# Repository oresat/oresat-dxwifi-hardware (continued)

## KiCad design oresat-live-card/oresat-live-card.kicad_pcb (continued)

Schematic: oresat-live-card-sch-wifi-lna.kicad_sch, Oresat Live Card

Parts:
C90, C91, C93: 15p; 0402-C-NOSILK; MPN GJM1555C1H150JB01D
C92: 1u; 0603-C-NOSILK; MPN GRT188R71E105KE13D
C106, C111: 0.1u; 0603-C-NOSILK; MPN C0603C104K5RACAUTO
C107, C114: 100p; 0402-C-NOSILK; MPN GCM1555C1H101GA16D
C108: 1n; 0402-C-NOSILK; MPN C0402C102J1GACTU
C109: 1n; 0402-C-NOSILK; MPN CGA2B2NP01H102J050BA
C110: 1p; 0402-C-NOSILK; MPN GCM1555C1H1R0CA16J
C112, C113: 100n; 0402-C-NOSILK; MPN CGA2B3X7R1E104K050BB
D15: GRN; LED-0603; MPN 150060GS75000
FL1, FL2: QPQ1907SR; MPN QPQ1907SR
L3: 18n; 0603-C-NOSILK; MPN 0603DC-18NXJRW
L4: 1.5n; 0402-C-NOSILK; MPN 0402HM-1N5EKTS
R85: 4.7k; 0603-C-NOSILK; MPN RMCF0603FT4K70
R88: 10k; 0603-C-NOSILK; MPN RMCF0603FT10K0
R105: 33k; 0603-C-NOSILK; MPN RMCF0603FT33K0
R106: 0; 0402-C-NOSILK; MPN RMCF0402ZT0R00
R109: 56; 0603-C-NOSILK; MPN ERJ-3EKF56R0V
R118, R119, R120: 4.99k; 0603-C-NOSILK; MPN RMCF0603FT4K99
R121: 100; 0603-C-NOSILK; MPN RMCF0603FT100R
TP26: TEST-POINT3X4; TestPoint-0.75mm-th
U18: TQP3M9037; DFN-8-1EP_2x2mm_P0.5mm_EP0.8x1.6mm; MPN TQP3M9037
U27: PAT1220-C-3DB; RF_Attenuator_Susumu_PAT1220; MPN PAT1220-C-3DB-T5
U28: PD2328J5050S2HF; MPN PD2328J5050S2HF
U29: LTC5538; DFN-8-1EP_3x3mm_P0.5mm_EP1.65x2.38mm; MPN LT5538IDD#TRPBF

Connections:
5VA: C106.2, C107.1, C112.2, C113.2, C114.1, R106.2, R118.1, U29.5 (VCC); also elsewhere on the board
/SIP B: ADC + Crystals/RF/RX_IN_DETECTED: C111.1, R119.2, R120.2, TP26.1 (1_1); also elsewhere on the board
/WiFi LNA/AR9271_RX: R121.1, U28.4 (OUTPUT1); also elsewhere on the board
/WiFi LNA/LNA_SHUTDOWN: R85.1, R105.1; also elsewhere on the board
/WiFi LNA/RX_FROM_SWITCH: FL1.1 (INPUT); also elsewhere on the board
GND: C91.2, C92.2, C106.1, C107.2, C108.2, C110.1, C111.2, C114.2, D15.1 (K), FL1.2 (GND), FL1.3 (GND), FL1.5 (GND), FL2.2 (GND), FL2.3 (GND), FL2.5 (GND), R88.2, R109.2, R120.1, U18.9 (GND), U27.3, U28.1 (GND), U28.3 (GND), U28.5 (GND), U29.4 (GND), U29.9 (GND); also elsewhere on the board
unnamed: C91.1, C92.1, L3.1, R106.1
unnamed: C93.2, U27.1
unnamed: C109.1, L4.2, R109.1
unnamed: D15.2 (A), R85.2
unnamed: C90.1, FL1.4 (OUTPUT)
unnamed: FL2.1 (INPUT), U27.2
unnamed: FL2.4 (OUTPUT), U28.2 (INPUT)
unnamed: C90.2, U18.2 (RF_IN)
unnamed: C93.1, L3.2, U18.7 (RF_OUT)
unnamed: R88.1, R105.2, U18.6 (SHUT_DOWN)
unnamed: C110.2, L4.1, R121.2, U28.6 (OUTPUT2)
unnamed: C113.1, U29.7 (CAP+)
unnamed: C112.1, U29.6 (CAP-)
unnamed: R118.2, U29.1 (EN)
unnamed: C109.2, U29.2 (IN+)
unnamed: C108.1, U29.3 (IN-)
unnamed: R119.1, U29.8 (OUT)

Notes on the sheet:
~ 1.65 V max which is < 1.8 V of Octavo ADC max
0402
Changed from 100 to 56
~ 3 V max
RF Detector, transforms RF detected into a DC sense line for Octavo to read
All resistors 0603 +/- 1% unless marked and AEQ certified unless otherwise marked. All caps are 0603 10% X5R or better and Vw >= 25 V and AEQ certified unless otherwise marked.
"LNA OFF"

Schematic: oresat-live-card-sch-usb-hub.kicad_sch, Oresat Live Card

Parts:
C1, C27, C28, C42, C54, C55, C56, C57, C58, C59, C60, C65, C66, C67, C68, C70, C71, C72: 0.1u; 0603-C-NOSILK; MPN C0603C104K5RACAUTO
C53, C69, C76, C96, C97: 10u; 0805-C-NOSILK; MPN GRT21BC71E106KE13K
C63, C64: 12p; 0603-C-NOSILK; MPN C0603C120J1GACTU
C73: 1u; 0603-C-NOSILK; MPN GRT188R71E105KE13D
D10: GRN; LED-0603; MPN 150060GS75000
FB1, FB3: BLM18KG300TH1D; 0603; MPN BLM18KG300JH1D
FB4, FB5: MMZ1608Y221BTD25; 0603; MPN MMZ1608Y221BTD25
R6, R7, R21, R76, R77, R79, R89, R90, R91: 10k; 0603-C-NOSILK; MPN RMCF0603FT10K0
R29: 4.7k; 0603-C-NOSILK; MPN RMCF0603FT4K70
R78: 9.53k; 0603-C-NOSILK; MPN RMCF0603FT9K53
R83: 90.9k; 0603-C-NOSILK; MPN RMCF0603FT90K9
R98, R99: 0; 0603-C-NOSILK; MPN RMCF0603ZT0R00
TP1, TP15: TEST-POINT; TestPoint_Pad_D1.0mm
TP13, TP16, TP17, TP18: TEST-POINT3X4; TestPoint_Pad_D1.0mm
U2: TUSB4020BI; TQFP-48-1EP_7x7mm_P0.5mm_EP5x5mm; MPN TUSB4020BIPHPRQ1
U9, U20: TPS2041BQDBVRQ1; DBV5; MPN TPS2041BQDBVRQ1
Y3: 24MHz; 5X3.2-4SMD; MPN ECS-240-12-30BQ-AEN-TR

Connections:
1.1V: FB4.2; also elsewhere on the board
+3.3V: FB5.2, R6.2, R7.2, R77.1, R79.2, R90.2, R91.2; also elsewhere on the board
+5V: R98.2, R99.2; also elsewhere on the board
/SIP B: ADC + Crystals/UP_N: U2.27 (USB_DM_UP); also elsewhere on the board
/SIP B: ADC + Crystals/UP_P: U2.26 (USB_DP_UP); also elsewhere on the board
/SIP B: ADC + Crystals/USB_VBUS: R83.1; also elsewhere on the board
/SIP C: SD + eMMC + CAN/GRSTz: R89.2, U2.11 (GRSTz); also elsewhere on the board
/USB HUB/CAMERA_USB_N: U2.42 (USB_DM_DN1); also elsewhere on the board
/USB HUB/CAMERA_USB_P: U2.41 (USB_DP_DN1); also elsewhere on the board
/USB HUB/CAMERA_VUSB: FB3.2, TP1.1 (1_1); also elsewhere on the board
/USB HUB/WIFI_ENABLE: R29.1; also elsewhere on the board
/USB HUB/WIFI_STATUS: D10.1 (K); also elsewhere on the board
/USB HUB/WIFI_USB_N: U2.15 (USB_DM_DN2); also elsewhere on the board
/USB HUB/WIFI_USB_P: U2.14 (USB_DP_DN2); also elsewhere on the board
/USB HUB/WIFI_VUSB: FB1.2, R21.1, R29.2, TP15.1 (1_1); also elsewhere on the board
GND: C1.2, C27.2, C28.2, C42.2, C53.2, C54.2, C55.2, C56.2, C57.2, C58.2, C59.2, C60.2, C63.2, C64.2, C65.2, C66.2, C67.2, C68.2, C69.2, C70.2, C71.2, C72.2, C73.2, C76.2, C96.2, C97.2, R76.1, R78.2, R89.1, U2.10 (TEST), U2.49 (GND), U9.2 (GND), U20.2 (GND), Y3.2 (G), Y3.4 (G); also elsewhere on the board
unnamed: C54.1, C55.1, C57.1, C59.1, C65.1, C67.1, C69.1, FB4.1, U2.1 (VDD), U2.12 (VDD), U2.18 (VDD), U2.30 (VDD), U2.34 (VDD), U2.45 (VDD)
unnamed: D10.2 (A), R21.2
unnamed: TP13.1 (1_1), U2.36 (FULLPWRMGMTz/SMBA1)
unnamed: R79.1, U2.35 (GANGED/SMBA2/HS_UP)
unnamed: R91.1, U2.5 (OVERCUR1z), U20.3 (~OC)
unnamed: R6.1, U2.8 (OVERCUR2z), U9.3 (~OC)
unnamed: R90.1, U2.4 (PWRCTL1/BATEN1), U20.4 (~EN)
unnamed: R7.1, U2.6 (PWRCTL2/BATEN2), U9.4 (~EN)
unnamed: R77.2, U2.21 (PWRCTL_POL)
unnamed: TP17.1 (1_1), U2.2 (SCL/SMBCLK)
unnamed: TP16.1 (1_1), U2.3 (SDA/SMBDAT)
unnamed: TP18.1 (1_1), U2.22 (SMBUSz)
unnamed: R78.1, U2.24 (USB_R1)
unnamed: R76.2, R83.2, U2.9 (USB_VBUS)
unnamed: C63.1, U2.38 (XI), Y3.1
unnamed: C64.1, U2.39 (XO), Y3.3
unnamed: C1.1, R98.1, U9.5 (IN)
unnamed: C27.1, C53.1, C96.1, FB3.1, U9.1 (OUT)
unnamed: C28.1, R99.1, U20.5 (IN)
unnamed: C42.1, C76.1, C97.1, FB1.1, U20.1 (OUT)
VDD33: C56.1, C58.1, C60.1, C66.1, C68.1, C70.1, C71.1, C72.1, C73.1, FB5.1, U2.7 (VDD33), U2.13 (VDD33), U2.23 (VDD33), U2.25 (VDD33), U2.33 (VDD33), U2.37 (VDD33), U2.40 (VDD33), U2.48 (VDD33)

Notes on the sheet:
Wifi USB
Ordering of ferrite bead and capacitor taken from TPS2041 datasheet (see figure 9-13)
Assert GRSTz via GPIO to deactivate USB hub and clear registers
Camera USB
"WIFI"
All resistors 0603 +/- 1% unless marked and AEQ certified unless otherwise marked. All caps are 0603 10% X5R or better and Vw >= 25 V and AEQ certified unless otherwise marked.

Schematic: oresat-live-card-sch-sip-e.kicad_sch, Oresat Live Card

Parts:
U7: OSD3358-512M-BSM; U-Octavo-OSD335X-BGA-256; MPN OSD3358-512M-BSM

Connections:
GND: U7.D8 (DGND@1), U7.D9 (DGND@2), U7.E5 (DGND@3), U7.E6 (DGND@4), U7.E7 (DGND@5), U7.E8 (DGND@6), U7.E9 (DGND@7), U7.E10 (DGND@8), U7.E11 (DGND@9), U7.E12 (DGND@10), U7.F5 (DGND@11), U7.F12 (DGND@12), U7.G5 (DGND@13), U7.G12 (DGND@14), U7.H4 (DGND@15), U7.H5 (DGND@16), U7.H12 (DGND@17), U7.H13 (DGND@18), U7.J4 (DGND@19), U7.J5 (DGND@20), U7.J12 (DGND@21), U7.J13 (DGND@22), U7.K5 (DGND@23), U7.K12 (DGND@24), U7.L5 (DGND@25), U7.L12 (DGND@26), U7.M5 (DGND@27), U7.M6 (DGND@28), U7.M7 (DGND@29), U7.M8 (DGND@30), U7.M9 (DGND@31), U7.M10 (DGND@32), U7.M11 (DGND@33), U7.M12 (DGND@34), U7.N8 (DGND@35), U7.N9 (DGND@36); also elsewhere on the board

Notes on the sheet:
All resistors 0603 +/- 1% unless marked and AEQ certified unless otherwise marked. All caps are 0603 10% X5R or better and Vw >= 25 V and AEQ certified unless otherwise marked.

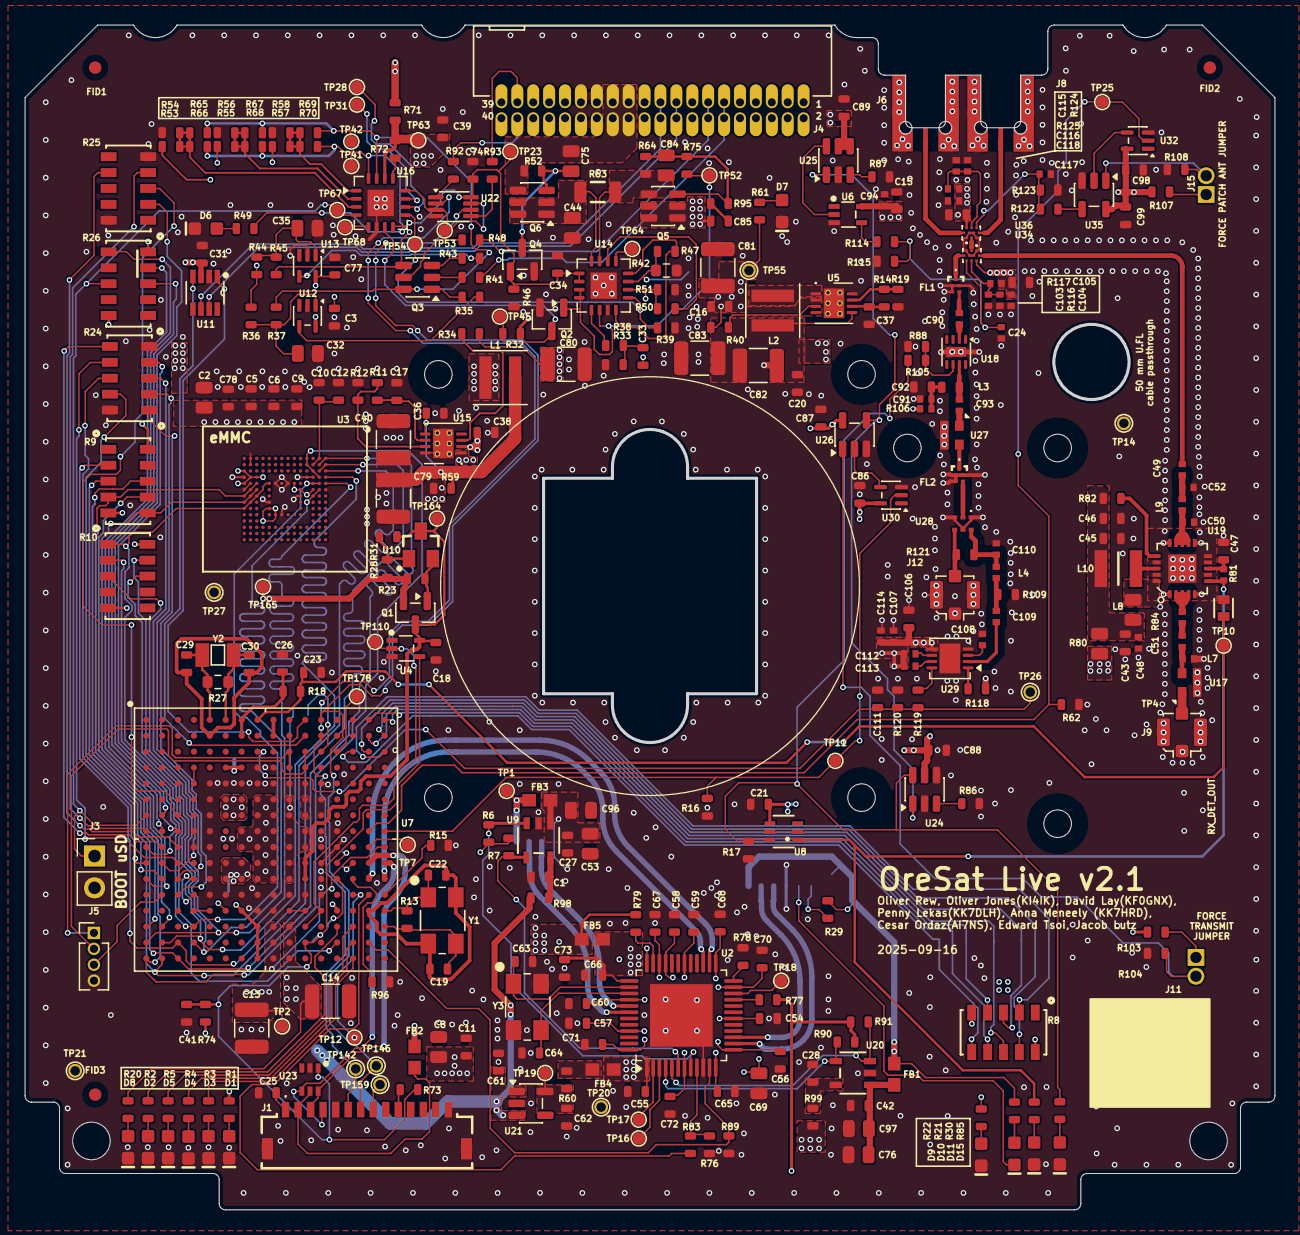
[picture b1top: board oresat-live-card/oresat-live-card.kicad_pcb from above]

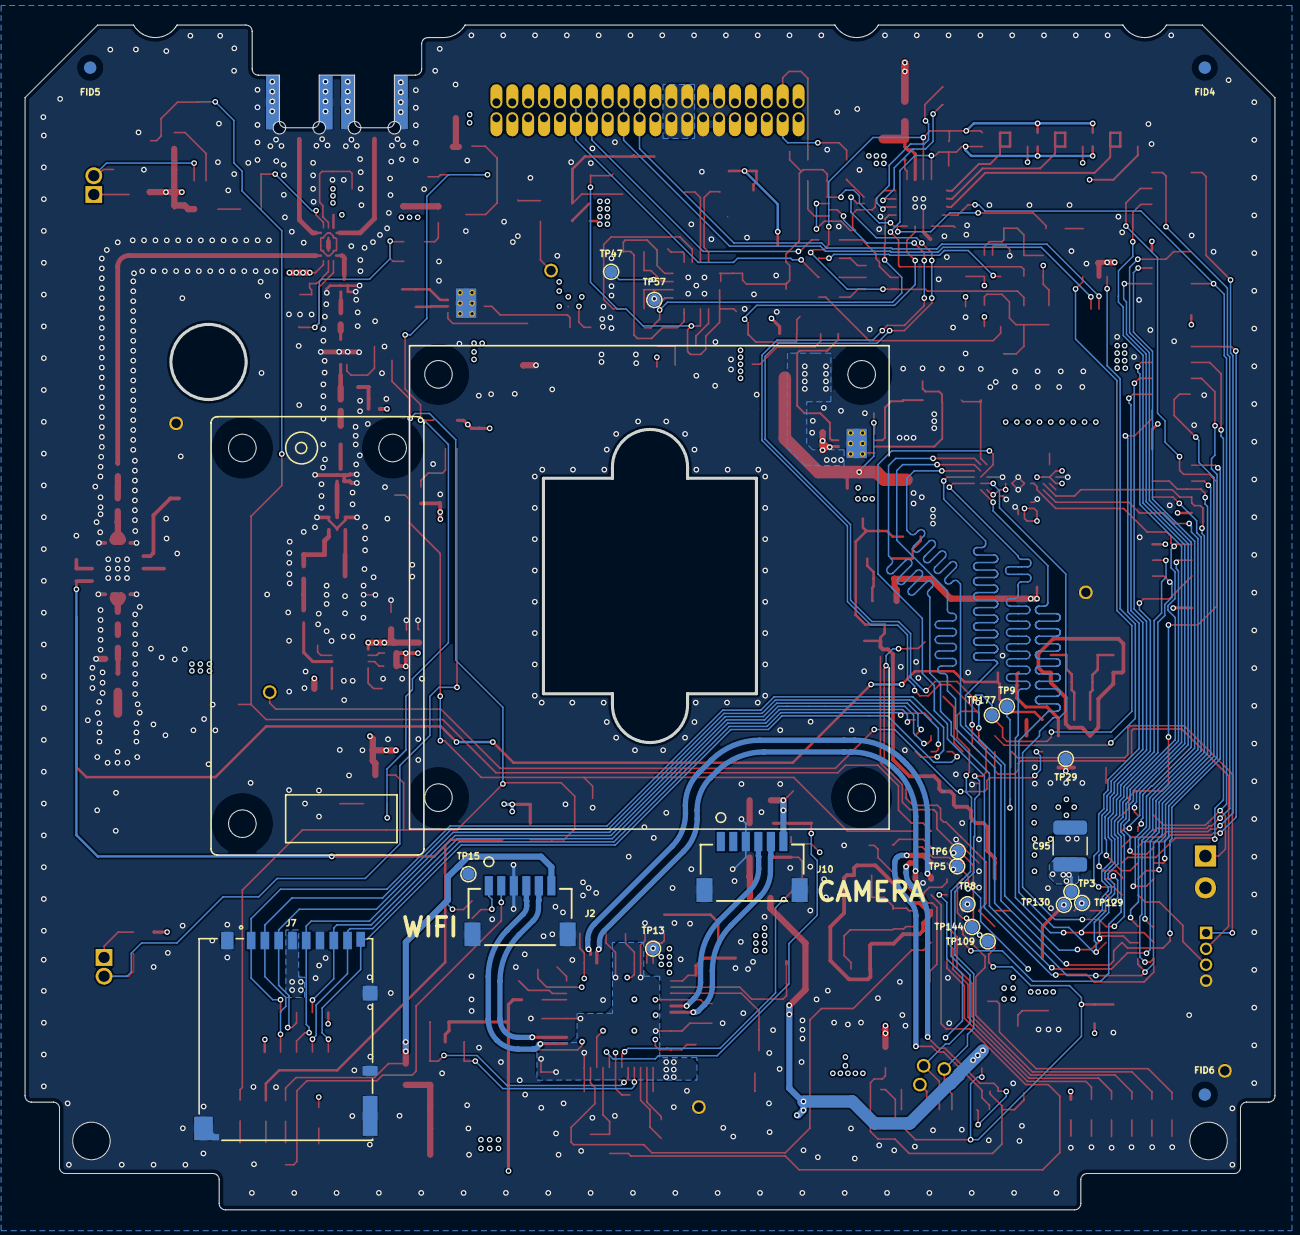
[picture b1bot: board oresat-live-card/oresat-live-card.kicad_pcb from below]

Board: 4 copper layers, 99.8 x 94.6 mm, 373 parts (23 on the bottom side), 246 nets.

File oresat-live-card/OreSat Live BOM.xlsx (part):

Qty_per_CCA | Reference(s) | Value | DESCRIPTION | MFR | MPN | Digi-Key PN | Alt MFR | Alt MPN | Notes
34 | C1, C3, C4, C7, C11, C15, C18, C21, C23, C28, C31, C39, C41, C42, C43, C45, C46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 | 0.1uF | CAP CER 0.1UF 25V X7R 0603 | TDK Corporation | CGA3E2X7R1E104K080AA | 445-5667-1-ND
10 | C2, C8, C16, C27, C38, C44, C53, C69, C75, C76 | 10uF | CAP CER 10UF 16V X7S 0805 | TDK Corporation | CGA4J1X7S1C106M125AC | 445-16111-1-ND
11 | C5, C6, C9, C10, C12, C33, C34, C61, C62, C73, C78 | 1uF | CAP CER 1UF 16V X7R 0603 | TDK Corporation | CGA3E1X7R1C105K080AC | 445-12539-1-ND
2 | C13, C14 | 22uF | CAP CER 22UF 16V X7R 1210 | TDK Corporation | CGA6P1X7R1C226M250AC | 445-5723-1-ND
2 | C17, C37 | 2.2uF | CAP CER 2.2UF 16V X7R 0603 | Murata | GRM188Z71C225ME43J
6 | C19, C22, C29, C30, C63, C64 | 12pF | CAP CER 12PF 50V C0G 0603 | TDK Corporation | CGA3E2C0G1H120J080AA
2 | C20, C36 | 47uF | CAP CER 47UF 16V 1206 | KYOCERA AVX | 1206YD476MAT2A | 478-1206YD476MAT2ACT-ND
2 | C24, C25 | 1000PF | CAP CER 1000PF 100V X7R 0805 | TDK Corporation | CGA4F2X7R2A102K085AE | 445-173649-1-ND
1 | C26 | 0.1uF | CAP CER 0.1UF 50V X7R 0805 | TDK Corporation | CGA4J2X7R1H104K125AE | 445-5689-1-ND
2 | C32, C35 | 1uF | CAP CER 1UF 16V X7R 0805 | TDK Corporation | CGA4J2X7R1C105K125AA | 445-5689-1-ND
1 | C48 | 1000pF | CAP CER 1000PF 50V NP0 0402 | TDK Corporation | CGA2B2NP01H102J050BA | 445-12118-1-ND
1 | C49 | 100pF | CAP CER 100PF 50V C0G/NP0 0402 | Murata | GCM1555C1H101GA16D | 490-GCM1555C1H101GA16DCT-ND
1 | C50 | 3.0pF | CAP CER 3PF 50V NP0 0402 | KYOCERA AVX | 04025U3R0BAT2A
1 | C51 | 1.1pF | 50V 1.1pF .02pFTol ThinFilm 0402 | KYOCERA AVX | 04025J1R1PBSTR\500
1 | C52 | 1.6pF | CAP CER 1.6PF 50V NP0 0402 | KYOCERA AVX | 04025U1R6BAT2A
8 | D1, D6, D7, D8, D9, D10, D11, D12 | GREEN | Green 525nm LED 3.2V 0603 | Würth Elektronik | 150060GS75020 | 732-150060GS75020CT-ND
4 | D2, D3, D4, D5 | BLUE | Blue 470nm LED 3.2V 0603 | Würth Elektronik | 150060BS75020 | 732-150060BS75020CT-ND
3 | FB1, FB2, FB3 | 30@100MHz | FERRITE BEAD 30 OHM 0603 1 LN | Murata Electronics | BLM18KG300TH1D | 490-13263-1-ND | Murata Electronics | BLM18KG300JH1D
2 | FB4, FB5 | 220@100MHz | FERRITE BEAD 220 OHM 0603 1LN | TDK Corporation | MMZ1608Y221BTD25 | 445-181786-1-ND
1 | J1 | ORESAT-DEBUG-CONNECTOR-CARD | CONN FPC BOTTOM 20POS 0.50MM R/A | TE Connectivity AMP Connectors | 2-1734592-0 | A100287CT-ND
2 | J2, J10 |  | CONN HEADER SMD R/A 6POS 1MM | JST Sales America Inc. | SM06B-SRSS-TB |  |  | Need alt
1 | J4 |  | CONN HEADER R/A 40POS 1.27MM | Samtec Inc. | TFM-120-01-L-D-RA | SAM10145-ND
1 | J5 |  | 2X1_TH_JUMPER
1 | J6 |  | CONN SMPM PLUG STR EDGEMNT | MOLEX | 0733000020 | WM10772-ND
1 | J7 |  | CONN MICRO SD CARD PUSH-PUSH R/A | Hirose Electric Co Ltd | DM3BT-DSF-PEJS |  |  | Need alt
1 | J9 |  | CONN U.FL RCPT STR 50 OHM SMD | Hirose Electric Co Ltd | U.FL-R-SMT-1(10)
2 | L1, L2 | 3.3uH | FIXED IND 3.3UH 6.6A 34MOHM SMD | Coilcraft | XGL4020-332MEC | 2457-XGL4020-332MEC-ND
1 | L7 | 1.7nH | 1.7nH RF Inductor, ceramic core, 5% tol | Coilcraft | 0402DC-1N7XJRW | 2457-0402DC-1N7XJRW-ND | Coilcraft | 0402DC-1N7XJRU
1 | L8 | 6.8nH | Fixed Inductors 0805CS 6.8 nH 5 % 0.6 A | Coilcraft | 0805CS-060XJLC
1 | L9 | 1.0nH | FIXED IND 1NH 500MA 100 MOHM SMD | TDK Corporation | MLK1005S1N0ST000 | 445-1455-1-ND
1 | L10 | 10nH | Fixed Inductors 1008 10nH Unshld 5% | Coilcraft | 1008HQ-10NXJLB
1 | Q1 |  | TRANS PNP 60V 0.6A SOT23-3 | Nexperia USA Inc. | PMBT2907A,215 | 1727-2958-1-ND | Diodes Incorporated | MMBT2907A-7-F
2 | Q2, Q4 |  | MOSFET N-CH 30V 4.1A TO236AB | Nexperia USA Inc. | PMV45EN2R
1 | Q3 |  | MOSFET 2P-CH 20V 2A SOT-26 | Diodes Incorporated | DMP2240UDM-7 |  | Taiwan Semiconductor Corp | TSM3911DCX6 RFG
2 | Q5, Q6 |  | MOSFET P CH 30V 4.5A TSOT26 | Diodes Incorporated | DMP3056LDM-7 | DMP3056LDMDICT-ND | Diodes Incorporated | DMP3050LVT-7
11 | R1, R2, R3, R4, R5, R20, R22, R29, R30, R49, R62 | 4.7k | RES SMD 4.7K OHM 1% 1/10W 0603 | Panasonic | ERJ-3EKF4701V | P4.70KHCT-ND |  | ERJ-U03F4701V
27 | R6, R7, R15, R16, R17, R18, R21, R28, R32, R34, R38, R39, R40, R46, R52, R54, R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 | 10k | RES SMD 10K OHM 1% 1/10W 0603 | Panasonic | ERJ-3EKF1002V |  |  | ERJ-U03F1002V
3 | R8, R9, R10 | 10k | RES ARRAY 8 RES 10K OHM 2512 | Panasonic | EXB-A10P103J | U7103CT-ND
6 | R11, R12, R14, R19, R33, R50 | 100k | RES SMD 100K OHM 1% 1/4W 0603 | Panasonic | ERJ-PA3F1003V |  |  | ERJ-U03F1003V
3 | R13, R36, R44 | 1M | RES SMD 1M OHM 1% 1/10W 0603 | Panasonic | ERJ-3EKF1004V |  |  | ERJ-U03F1004V
1 | R23 | 499 | RES SMD 499 OHM 1% 1/10W 0603 | Panasonic | ERJ-3EKF4990V |  |  | ERJ-U03F4990V
3 | R24, R25, R26 | 100K | RES ARRAY 8 RES 100K OHM 2512 | Panasonic | EXB-A10P104J | U7104CT-ND
1 | R31 | 40.2K | RES SMD 40.2K OHM 1% 1/10W 0603 | Panasonic | ERJ-3EKF4022V | P40.2KHCT-ND |  | ERJ-U03F4022V
2 | R35, R43 | 665k | RES SMD 665K OHM 1% 1/10W 0603 | Panasonic | ERJ-3EKF6653V | P665KHCT-ND |  | ERJ-U03F6653V
2 | R37, R45 | 330k | RES SMD 330K OHM 1% 1/10W 0603 | Panasonic | ERJ-3EKF3303V | P330KHCT-ND |  | ERJ-U03F3303V
6 | R41, R48, R71, R73, R74, R75 | 100 | RES SMD 100 OHM 1% 1/10W 0603 | Panasonic | ERJ-3EKF1000V | P100HCT-ND |  | ERJ-U03F1000V
5 | R47, R59, R60, R86, R94 | 0 | RES SMD 0 OHM JUMPER 1/10W 0603 | Panasonic | ERJ-3GEY0R00V |  |  | ERJ-U030R00V
1 | R51 | 20k | RES SMD 20K OHM 1% 1/10W 0603 | Panasonic | ERJ-3EKF2002V
1 | R63 | 100m | RES 0.1 OHM 1% 1/2W 1206 | Vishay Dale | RCWE1206R100FKEA
1 | R78 | 9.53k | RES 9.53K OHM 1% 1/10W 0603 | Panasonic | ERJ-3EKF9531V | P9.53KHCT-ND
1 | R80 | 0 | RES SMD 0 OHM JUMPER 1/8W 0805 | Panasonic | ERJ-6GEY0R00V |  |  | ERJ-U060R00V
1 | R81 | 110 | RES SMD 110 OHM 1% 1/10W 0402 | Panasonic | ERJ-2RKF1100X | P110LCT-ND |  | ERJ-U02F1100X
1 | R82 | 220 | RES SMD 220 OHM 1% 1/10W 0603 | Panasonic | ERJ-3EKF2200V | P220HCT-ND |  | ERJ-U03F2200V
1 | R83 | 90.9k | RES SMD 90.9K OHM 1% 1/10W 0603 | Panasonic | ERJ-3EKF9092V |  |  | ERJ-U03F9092V
1 | R84 | 3.3 | RES SMD 3.3 OHM 1% 1/16W 0402 | Vishay / Dale | CRCW04023R30FKED | 541-3.30LLCT-ND
0 | R85 DNP | 82.5 | RES SMD 82.5 OHM 1% 1/10W 0603 | Panasonic | ERJ-3EKF82R5V | P82.5HCT-ND |  | ERJ-U03F82R5V
0 | R86 DNP | 93.1 | RES SMD 93.1 OHM 1% 1/10W 0603 | Panasonic | ERJ-3EKF93R1V | P93.1HCT-ND |  | ERJ-U03F93R1V
0 | R87, R88 DNP | 41.2 | RES SMD 41.2 OHM 1% 1/10W 0603 | Panasonic | ERJ-3EKF41R2V | P41.2HCT-ND |  | ERJ-U03F41R2V
2 | R92, R93 | 1k | RES SMD 1K OHM 1% 1/10W 0603 | Panasonic | ERJ-3EKF1001V | P1.00KHCT-ND |  | ERJ-U03F1001V
1 | RT1 |  | THERMISTOR NTC 10KOHM 3380K 0603 | TDK Corporation | NTCG163JX103DT1S | 445-174518-1-ND
2 | U1, U18 |  | TVS DIODE 5V 17.5V SC70-6 | Semtech Corporation | RCLAMP0504FBTCT | RCLAMP0504FBTCTCT-ND
1 | U2 |  | IC USB 2.0 2PORT HUB IND 48HTQFP | Texas Instruments | TUSB4020BIPHPRQ1 |  |  | Need alt
1 | U3 |  | IC FLASH 16GBIT EMMC 153FBGA | ATP Electronics, Inc. | AF016GEC5X-2001A2 | 1282-AF016GEC5X-2001A2-ND | Kioxia | THGBMJG7C2LBAU8
1 | U4 |  | IC BUF NON-INVERT 5.5V SC70-5 | Texas Instruments | SN74AUC1G07DCKR | 296-12464-1-ND | Texas Instruments | SN74LVC1G07DCK3
2 | U5, U15 |  | IC REG BUCK 5V 2A 8DFN | Analog Devices | LTC3624IDD-5#PBF | LTC3624IDD-5#PBF-ND
1 | U6 |  | IC GATE OR 1CH 2-INP SOT23-5 | Texas Instruments | SN74AHC1G32TDBVRQ1 | 296-17421-1-ND | Texas Instruments | SN74LVC1G32QDBVRQ1
1 | U7 |  | OSD335x Embedded Module 1GHz 512MB | Octavo Systems | OSD3358-512M-BSM
1 | U8 |  | IC PWR SWITCH P-CHAN 1:1 SC70-6 | Microchip Technology |  | MIC94070YC6 | Microchip Technology | MIC94090YC6
2 | U9, U20 |  | Power Switch/Driver 1:1 N-Channel 500mA | Texas Instruments | TPS2041BQDBVRQ1
1 | U10 |  | IC VREF SHUNT 18V 0.5% SOT23-3 | Texas Instruments | TLVH431BCDBZT | 296-32429-1-ND | Texas Instruments | TLVH431BQDBZRQ1
1 | U11 |  | IC TRANSCEIVER 1/1 SOT23-8 | Texas Instruments | TCAN330GDCN |  | Analog Devices | MAX33040EAKA | Try Lanka Micro for TI part. Ground TP40 (pin 8) if using Max part.
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
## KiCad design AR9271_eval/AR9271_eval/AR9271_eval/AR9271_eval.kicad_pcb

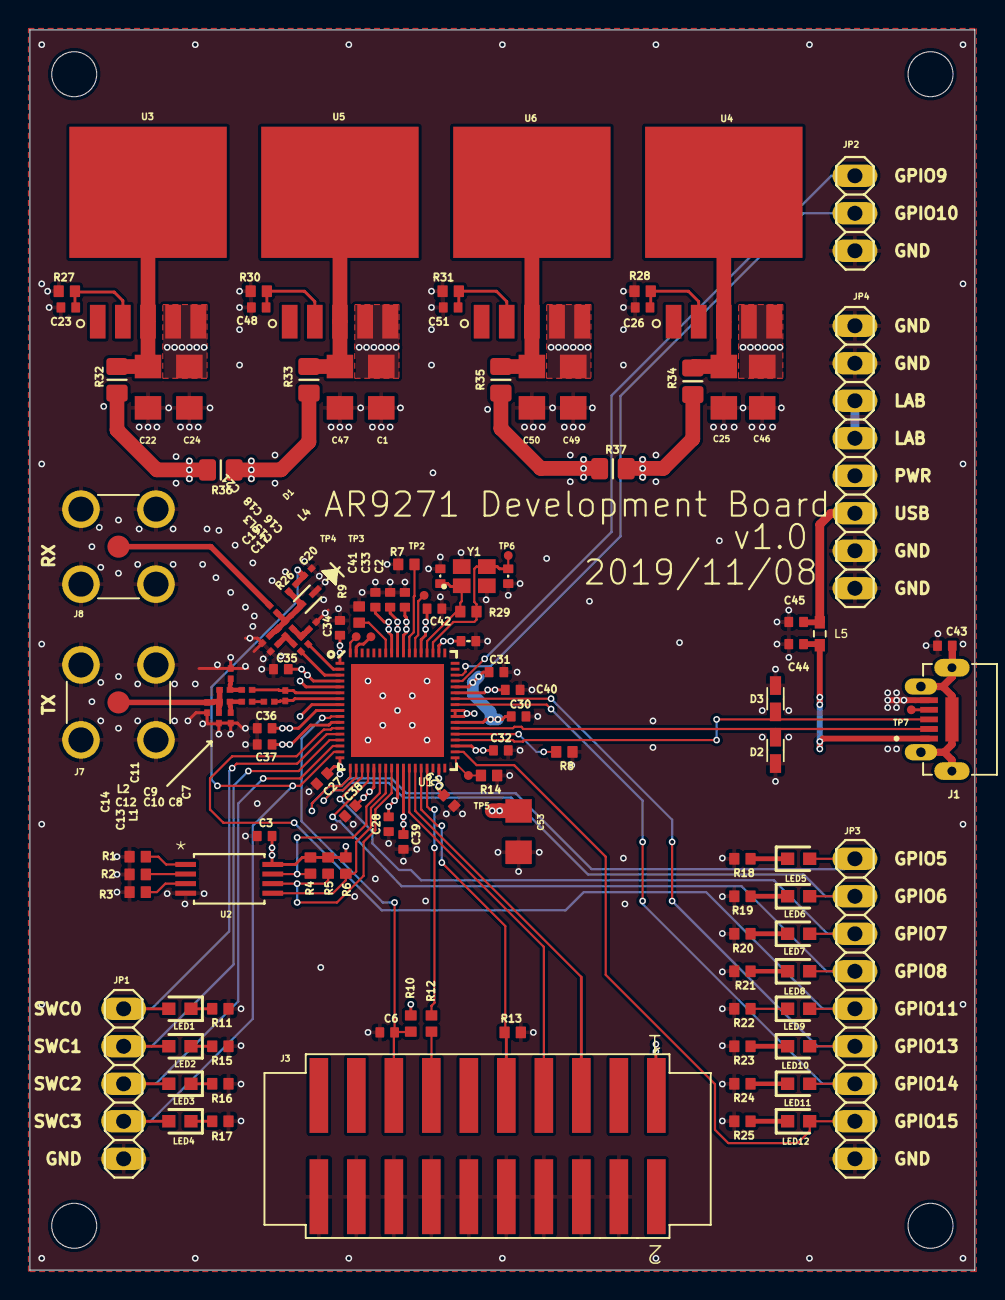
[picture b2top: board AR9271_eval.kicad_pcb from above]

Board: 4 copper layers, 64.0 x 84.0 mm, 135 parts (0 on the bottom side), 80 nets.

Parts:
C1, C22, C24, C25, C46, C47, C49, C50, C53: 4.7uF; C1206_334
C2, C3, C6, C26, C27, C28, C29, C30, C31, C32, C33, C34, C43, C45, C51: 100n; .0402-B-NOSILK
C4, C5, C35, C36: 10p; .0402-B-NOSILK
C7: 2.2pF; .0201-B-NOSILK
C8, C9, C15, C16, C20: 10.0pF; .0201-B-NOSILK
C10, C11, C12, C13: 2.0pF; .0201-B-NOSILK
C14, C19: 1.0pF; .0201-B-NOSILK
C17, C18: 1.5pF; .0201-B-NOSILK
C21: 100.0pF; .0201-B-NOSILK
C23, C48: 10nF; .0402-B-NOSILK
C37: 100p; .0402-B-NOSILK
C38, C40: 1n; .0402-B-NOSILK
C39, C44: 10n; .0402-B-NOSILK
C41, C42, C52: 1u; .0402-B-NOSILK
D1: SMP1321-079LF; SOD523
D2, D3: PGB1010603MR; ESD_PGB1010603MR
H1, H2, H3, H4: STAND-OFFTIGHT; STAND-OFF-TIGHT_519
J1: UJ2-MIBH2-4-SMT-TR; CUI_UJ2-MIBH2-4-SMT-TR
J3: HTST-110-01-XX-DV
J7, J8: 132134-15; AMPHENOL_132134-15
JP1: 1X05_325
JP2: 1X03_325
JP3: 1X09_325
JP4: 1X08_325
L1, L2: 1.8nH; .0201-B-NOSILK
L3, L4: 2.2nH; .0201-B-NOSILK
L5: BLM18PG221SH1D; INDC1608X95
LED1, LED2, LED3, LED4, LED5, LED6, LED7, LED8, LED9, LED10, LED11, LED12: LTST-C193KGKT-5A; LEDC1607X80N
R1: DNP; .0402-A-NOSILK
R2, R3: 0; .0402-A-NOSILK
R4, R7, R10, R13, R14: 10k; .0402-A-NOSILK
R5, R6: 4.7k; .0402-A-NOSILK
R8: 51.1; .0402-A-NOSILK
R9: 6.19k; .0402-A-NOSILK
R11, R15, R16, R17, R18, R19, R20, R21, R22, R23, R24, R25: 510; .0402-A-NOSILK
R12: 33; .0402-A-NOSILK
R26: 1.0k; .0201-B-NOSILK
R27, R30: 330k; .0402-A-NOSILK
R28, R31: 120k; .0402-A-NOSILK
R29: 1M; .0402-A-NOSILK
R32, R33, R34, R35: 0; .0805-B
R36, R37: DNP; .0805-B
TP2, TP3, TP4, TP5, TP6, TP7: TPTP06R; TP06R_385
U1: U-ATHEROS-AR9271; QFN-68
U2: AT24C04C-XHM-T; 8X
U3, U4, U5, U6: LT3080EQPBF; DDPAK-5_Q
Y1: ECS-400-10-36-CKY-TR; XTAL_ECS-400-10-36-CKY-TR

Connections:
1V2_A: C2.1, C41.1, C42.1, R35.2, R37.1, U1.56, U1.59, U1.61
1V2_D: C37.1, C38.1, C39.1, C40.1, R34.2, R37.2, U1.11, U1.22, U1.27, U1.42, U1.43, U1.46
3V3_A: C33.1, C34.1, C35.1, C36.1, C52.1, R33.2, R36.1, U1.1, U1.4, U1.9, U1.53, U1.60
3V3_D: C3.1, C27.1, C28.1, C29.1, C30.1, C31.1, C32.1, C53.1, J3.1, R4.2, R5.2, R6.2, R10.2, R32.2, R36.2, U1.5, U1.8, U1.17, U1.26, U1.33, U1.37, U1.41, U1.47, U2.8
A1: R2.2, U2.2
A2: R3.2, U2.3
BIASREF: R9.1, U1.62
CTRL1: R7.2, U1.58
CTRL2: TP2.TP, U1.57
EE-SCK: R5.1, U1.25, U2.6
EE-SDA: R6.1, U1.24, U2.5
EE-WP: R4.1, U1.23, U2.7
GND: C1.2, C2.2, C3.2, C4.2, C5.2, C6.2, C11.1, C13.1, C14.2, C17.2, C19.2, C20.2, C22.2, C23.2, C24.2, C25.2, C26.2, C27.2, C28.2, C29.2, C30.2, C31.2, C32.2, C33.2, C34.2, C35.2, C36.2, C37.2, C38.2, C39.2, C40.2, C41.2, C42.2, C43.2, C44.2, C45.2, C46.2, C47.2, C48.2, C49.2, C50.2, C51.2, C52.2, C53.2, D1.1, D2.2, D3.2, J1.5, J3.4, J3.6, J3.8, J3.10, J3.12, J3.14, J3.16, J3.18, J3.20, J7.P1, J7.P2, J7.P3, J7.P4, J8.P1, J8.P2, J8.P3, J8.P4, JP1.5, JP2.3, JP3.9, JP4.1, JP4.2, JP4.7, JP4.8, L1.1, L4.1, R1.1, R2.1, R3.1, R7.1, R8.1, R9.2, R11.1, R13.1, R14.1, R15.1, R16.1, R17.1, R18.1, R19.1, R20.1, R21.1, R22.1, R23.1, R24.1, R25.1, R27.1, R28.1, R30.1, R31.1, U1.69, U2.4, Y1.2, Y1.4
GPIO5: JP3.1, LED5.2, U1.18
GPIO6: JP3.2, LED6.2, U1.19
GPIO7: JP3.3, LED7.2, U1.20
GPIO8: JP3.4, LED8.2, U1.21
GPIO9: JP2.1, U1.48
GPIO10: JP2.2, U1.49
GPIO11: JP3.5, LED9.2, U1.12
GPIO13: JP3.6, LED10.2, U1.45
GPIO14: JP3.7, LED11.2, U1.44
GPIO15: JP3.8, LED12.2, U1.36
LDO_IN: C1.1, C24.1, C46.1, C49.1, JP4.5, U3.4, U3.5, U4.4, U4.5, U5.4, U5.5, U6.4, U6.5
unnamed: J1.4, TP7.TP
unnamed: JP4.3, JP4.4
unnamed: R1.2, U2.1
unnamed: LED1.1, R11.2
unnamed: LED2.1, R15.2
unnamed: C10.2, C12.1, L1.2
unnamed: C15.2, C17.1, L3.1
unnamed: C16.2, C18.1, L4.2
unnamed: C9.2, C11.2, L2.1
unnamed: LED3.1, R16.2
unnamed: LED4.1, R17.2
unnamed: LED5.1, R18.2
unnamed: C8.2, C10.1
unnamed: C23.1, R27.2, U3.2
unnamed: C18.2, C19.1, C21.1, D1.2, L3.2, R26.2
unnamed: C26.1, R28.2, U4.2
unnamed: LED6.1, R19.2
unnamed: LED7.1, R20.2
unnamed: LED8.1, R21.2
unnamed: LED9.1, R22.2
unnamed: C43.1, J1.SH1, J1.SH2, J1.SH3, J1.SH4, J1.SH5
unnamed: C22.1, R32.1, U3.3, U3.6
unnamed: LED10.1, R23.2
unnamed: LED11.1, R24.2
unnamed: LED12.1, R25.2
unnamed: C25.1, R34.1, U4.3, U4.6
unnamed: C48.1, R30.2, U5.2
unnamed: C47.1, R33.1, U5.3, U5.6
unnamed: C51.1, R31.2, U6.2
unnamed: C50.1, R35.1, U6.3, U6.6
PDET: TP4.TP, U1.68
RCV_IN: C21.2, J8.1
RFIN_N: C16.1, U1.2
RFIN_P: C15.1, U1.3
RFOUT_N: C7.1, C9.1, U1.6
RFOUT_P: C7.2, C8.1, U1.7
SPIBOOT: R14.2, TP5.TP, U1.35
SWCOM0: JP1.1, LED1.2, U1.13
SWCOM1: JP1.2, LED2.2, U1.14
SWCOM2: JP1.3, LED3.2, U1.15
SWCOM3: C20.1, JP1.4, LED4.2, R26.1, U1.16
TCK: J3.9, R13.2, U1.30
TDI: J3.5, U1.29
TDO: J3.13, R12.2
TDO-PRE-RES: R12.1, U1.31
TMS: J3.7, U1.28
TXRTUNE: R8.2, U1.39
USB+5V: C45.1, JP4.6, L5.2
USB_+V: C44.1, J1.1, L5.1
USB_DM: D2.1, J1.2, U1.40
USB_DP: D3.1, J1.3, U1.38
XMIT_OUT: C12.2, C13.2, C14.1, J7.1, L2.2
XPABIOS: TP3.TP, U1.67
XTALI: C4.1, R29.1, U1.55, Y1.1
XTALO: C5.1, R29.2, TP6.TP, U1.54, Y1.3
~RST: C6.1, J3.15, R10.1, U1.10

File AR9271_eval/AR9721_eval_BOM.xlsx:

Bill Of Materials for AR9721
Source file: AR9721_eval.sch
Last modified: 2019/09/17
PCB version: 1.0 |  |  | P/DNP = | Place/Do Not Place (DNP is for final production boards)
BOM revision: 0 |  |  | Generic = | Any generic part with the same characteristics are OK (e.g., bypass cap)
Cnt | Part References | P/DNP | Mfg | Mfg PN | Description | Generic | Dist | Dist Part Number
9 | C1, C22, C24, C25, C46, C47, C49, C50, C53 | P | Murata Electronics | GCM31CR71C475KA37L | Capacitor, 4.7uF, 1206 | Y | Digi-key | 490-6065-1-ND
4 | C10, C11, C12, C13 | P | Taiyo Yuden | UMK063CG020CTHF | Capacitor, 2pF, 0201 | Y | Digi-key | 587-3777-2-ND
2 | C14, C19 | P | Taiyo Yuden | UMK063CG010CTHF | Capacitor, 1pF, 0201 | Y | Digi-key | 587-3776-1-ND
2 | C17, C18 | P | Taiyo Yuden | UMK063CG1R5CT-F | Capacitor, 1.5pF, 0201 | Y | Digi-key | 587-3202-6-ND
15 | C2, C3, C6, C26, C27, C28, C29, C30, C31, C32, C33, C34, C43, C45, C51 | P | TDK | CGA2B1X7R1C104K050BC | Capacitor, 100nF, 0402 | Y | Digi-key | 445-5613-1-ND
1 | C21 | P | Taiyo Yuden | UMK063CG101JT-F | Capacitor, 100pF, 0201 | Y | Digi-key | 587-3207-2-ND
4 | C23, C39, C44, C48 | P | Kemet | C0402C103K4RACAUTO | Capacitor, 10nF, 0402 | Y | Digi-key | 399-6825-1-ND
1 | C37 | P | TDK | CGA2B2C0G1H101J050BA | Capacitor, 100pF, 0402 | Y | Digi-key | 445-5596-1-ND
2 | C38, C40 | P | Kemet | C0402C102K5GACTU | Capacitor, 1nF, 0402 | Y | Digi-key | 399-7756-1-ND
4 | C4, C5, C35, C36 | P | Yageo | CC0402JRNPO9BN100 | Capacitor, 10pF, 0402 | Y | Digi-key | 311-1014-1-ND
3 | C41, C42, C52 | P | TDK | CGA2B2C0G1H100D050BA | Capacitor, 1uF, 0402 | Y | Digi-key | 445-5584-1-ND
1 | C7 | P | Taiyo Yuden | UMK063CG2R2CTHF | Capacitor, 2.2pF, 0201 | Y | Digi-key | 587-5314-1-ND
5 | C8, C9, C15, C16, C20 | P | Taiyo Yuden | UMK063CG100DTHF | Capacitor, 10pF, 0201 | Y | Digi-key | 587-3785-2-ND
1 | D1 | P | Skyworks | SMP1321-079 | RF PIN Diode | N | Digi-key | 863-1099-1-ND
2 | D2, D3 | P | Littelfuse Inc. | PGB1010603MR | PGB1 Series 15 V 63 Bi-Directional SMT ESD TVS | Y | Digi-key | F2594CT-ND
1 | J1 | P | CUI Inc. | UJ2-MIBH2-4-SMT-TR | Micro B Type 5 Pin Horizontal SMT USB Jack 2.0 | Y | Digi-key | 102-4007-1-ND
1 | J3 | P | Samtec Inc. | HTST-110-01-L-DV-P | Conn Shrouded Header HDR 20 POS 2.54mm Solder ST SMD | Y | Digi-key | SAM15675-ND
2 | J7, J8 | P | Amphenol RF | 132134-15 | Rf Coaxial, Sma, Straight Jack, Pcb | Y | Digi-key | ACX1962-ND
4 | JP1, JP2, JP3, JP4 | P | NA | NA | PIN HEADER | Y | Digi-key | 952-3308-ND
2 | L1, L2 | P | Murata Electronics | LQP03TN1N8B02D | Inductor, 1.8nH, 0201 | Y | Digi-key | 490-6720-1-ND
2 | L3, L4 | P | Murata Electronics | LQP03TN2N2B02D | Inductor, 2.2nH, 0201 | Y | Digi-key | 490-6723-1-ND
1 | L5 | P | Murata Electronics | BLM18PG221SH1D | FERRITE BEAD 220 OHM 0603 1LN | N | Digi-key | 490-7817-1-ND
12 | LED1, LED2, LED3, LED4, LED5, LED6, LED7, LED8, LED9, LED10, LED11, LED12 | P | Lite-On | LTST-C193KGKT-5A | LED,Green,0603, | Y | Digi-key | 160-1828-1-ND
3 | R1, R36, R37 | NP | NA | NA | NA | NA | NA | NA
12 | R11, R15, R16, R17, R18, R19, R20, R21, R22, R23, R24, R25 | P | Panasonic | ERJ-2GEJ511X | Resistor, 510, 0402 | Y | Digi-key | P510JTR-ND
1 | R12 | P | Panasonic | ERJ-2GEJ330X | Resistor, 33, 0402 | Y | Digi-key | P33JCT-ND
2 | R2, R3 | P | Panasonic | ERJ-2GE0R00X | Resistor, 0, 0402 | Y | Digi-key | P0.0JCT-ND
1 | R26 | P | Panasonic | ERJ-1GNF1001C | Resistor, 1k, 0201 | Y | Digi-key | P122413CT-ND
2 | R27, R30 | P | Panasonic | ERJ-2RKF3303X | Resistor, 330k, 0402 | Y | Digi-key | P330KLCT-ND
2 | R28, R31 | P | Panasonic | ERJ-2RKF1203X | Resistor, 120k, 0402 | Y | Digi-key | P120KLCT-ND
1 | R29 | P | Panasonic | ERJ-2GEJ105X | Resistor, 1M, 0402 | Y | Digi-key | P1.0MJTR-ND
4 | R32, R33, R34, R35 | P | Panasonic | ERJ-6GEY0R00V | Resistor, 0, 0805 | Y | Digi-key | P0.0ACT-ND
5 | R4, R7, R10, R13, R14 | P | Panasonic | ERJ-2GEJ103X | Resistor, 10k, 0402 | Y | Digi-key | ERJ-2GEJ103X
2 | R5, R6 | P | Panasonic | ERJ-2GEJ103X | Resistor, 4.7k, 0402 | Y | Digi-key | P10KJCT-ND
1 | R8 | P | Panasonic | ERJ-2RKF51R1X | Resistor, 51.1, 0402 | Y | Digi-key | P51.1LCT-ND
1 | R9 | P | Panasonic | ERJ-2RKF6191X | Resistor, 6.19k, 0402 | Y | Digi-key | P6.19KLCT-ND
1 | U1 | P | Atheros | AR9271-AL1A | Atheros WiFi WLAN IC | N | AliExpress | N/A
1 | U2 | P | Microchip | AT24C04CXHMT | EEPROM with I2C interface | N | Digi-key | AT24C04C-XHM-TCT-ND
4 | U3, U4, U5, U6 | P | Analog Devices | LT3080EQ#PBF | Adj. 1.1A Single Res LDO Regulator | N | Digi-key | LT3080EQ#PBF-ND
1 | Y1 | P | ECS International | ECS-400-10-36-CKY-TR | Crystal 40mhz 10pf Smd | N | Digi-key | XC2666CT-ND
VERSION INFO
Rev | Date | Notes
1 | 43725 | First rev BOM

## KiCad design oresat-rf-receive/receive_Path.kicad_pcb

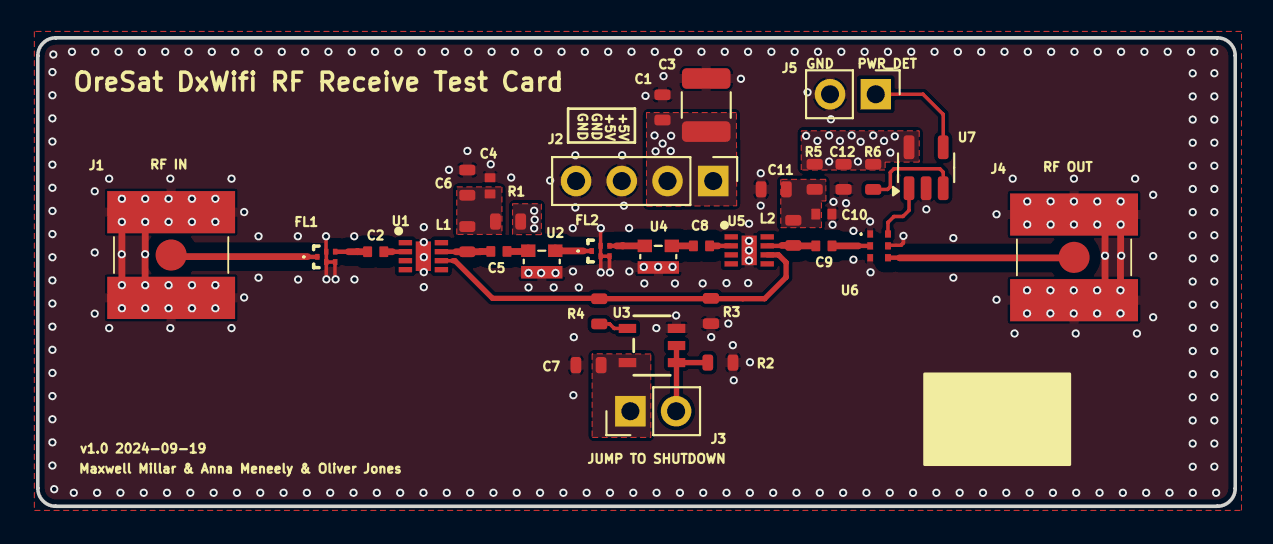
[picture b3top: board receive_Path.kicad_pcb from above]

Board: 4 copper layers, 66.5 x 26.0 mm, 34 parts (0 on the bottom side), 22 nets.

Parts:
C1: 2u2; 0603-C-NOSILK
C2, C4, C5, C8, C9, C10: 15p; 0402-C-NOSILK
C3: 22u; C_1210_3225Metric
C6, C11: 1u; 0603-C-NOSILK
C7, C12: 100n; 0603-C-NOSILK
FL1, FL2: QPQ1907SR
J1: 142-0711-201; SMA 142-0711-201
J2: 0022232041; PinHeader_1x04_P2.54mm_Vertical
J3, J5: 0022232021; PinHeader_1x02_P2.54mm_Vertical
J4: Conn_Coaxial_142-0711-201; SMA 142-0711-201
L1, L2: 18nH; 0603-C-NOSILK
R1, R5: 0; 0603-C-NOSILK
R2, R4: 10k; 0603-C-NOSILK
R3: 33K; 0603-C-NOSILK
R6: 10K; 0603-C-NOSILK
U1, U5: TQP3M9037
U2, U4: PAT1220-C-3DB; PAT1220(0805)
U3: SN74LVC1G32QDBVRQ1; DBV5 SN74LVC1G3T2Q
U6: PD2328J5050S2HF
U7: LTC5505-1ES5; TSOT-23-5

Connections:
5VA: C1.1, C3.1, C7.1, C12.1, J2.1, J2.2, J3.1, R1.2, R5.2, R6.2, U3.5 (VCC), U7.5 (VCC)
/PWR_DET_IN: U6.6 (OUTPUT2), U7.1 (RFIN)
/PWR_DET_OUT: J5.1, U7.4 (VOUT)
/RF_ATTEN1_OUT1: FL2.1 (INPUT), U2.2
/RF_ATTEN2_OUT1: C8.1, U4.2
/RF_ATTEN2_OUT2: C8.2, U5.2 (RF_IN)
/RF_BPF2_OUT: FL2.4 (OUTPUT), U4.1
/RF_BPF_OUT1: C2.1, FL1.4 (OUTPUT)
/RF_BPF_OUT2: C2.2, U1.2 (RF_IN)
/RF_IN: FL1.1 (INPUT), J1.3
/RF_LNA1_OUT1: C5.1, L1.2, U1.7 (RF_OUT)
/RF_LNA1_OUT2: C5.2, U2.1
/RF_LNA2_OUT1: C9.1, L2.2, U5.7 (RF_OUT)
/RF_LNA2_OUT2: C9.2, U6.2 (INPUT)
/RF_OUT1: J4.3, U6.4 (OUTPUT1)
GND: C1.2, C3.2, C4.2, C6.2, C7.2, C10.2, C11.2, C12.2, FL1.2 (GND), FL1.3 (GND), FL1.5 (GND), FL2.2 (GND), FL2.3 (GND), FL2.5 (GND), J1.1 (In), J1.2 (Ext), J2.3, J2.4, J4.1 (In), J4.2 (Ext), J5.2, R2.1, R3.1, U1.9 (GND), U2.3, U3.3 (GND), U4.3, U5.9 (GND), U6.1 (GND), U6.3 (GND), U6.5 (GND), U7.2 (GND)
unnamed: C4.1, C6.1, L1.1, R1.1
unnamed: C10.1, C11.1, L2.1, R5.1
unnamed: J3.2, R2.2, U3.1 (A), U3.2 (B)
unnamed: R3.2, R4.1, U1.6 (SHUT_DOWN), U5.6 (SHUT_DOWN)
unnamed: R4.2, U3.4 (Y)
unnamed: R6.1, U7.3 (~SHDN)
